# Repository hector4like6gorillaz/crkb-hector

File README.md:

# crkb-hector
diseños y pcb de teclados en eagle
Aqui tengo guardado lo que es mi pcb y esquematico de lo que viene a ser un teclado dividido en eagle cad soft tanto 
el lado derecho como el izquierdo diseñado en la version 8 del mismo programa antes mencionado

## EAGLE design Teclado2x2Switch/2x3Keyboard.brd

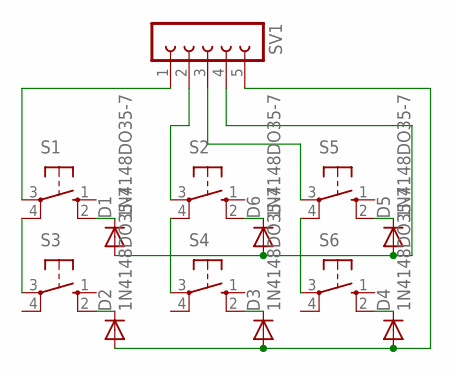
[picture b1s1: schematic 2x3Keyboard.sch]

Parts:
D1, D2, D3, D4, D5, D6: 1N4148DO35-7; DO35-7
S1, S2, S3, S4, S5, S6: 10-XX; B3F-10XX
SV1: FE05-1

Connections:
unnamed: S1.3, SV1.1
unnamed: S1.4 (P1), S3.3
unnamed: S2.4 (P1), S4.3
unnamed: S5.4 (P1), S6.3
unnamed: S2.3, SV1.2
unnamed: S5.3, SV1.3
unnamed: D1.C, S1.2 (S1)
unnamed: D6.C, S2.2 (S1)
unnamed: D5.C, S5.2 (S1)
unnamed: D4.C, S6.2 (S1)
unnamed: D3.C, S4.2 (S1)
unnamed: D2.C, S3.2 (S1)
unnamed: D2.A, D3.A, D4.A, SV1.5
unnamed: D1.A, D5.A, D6.A, SV1.4

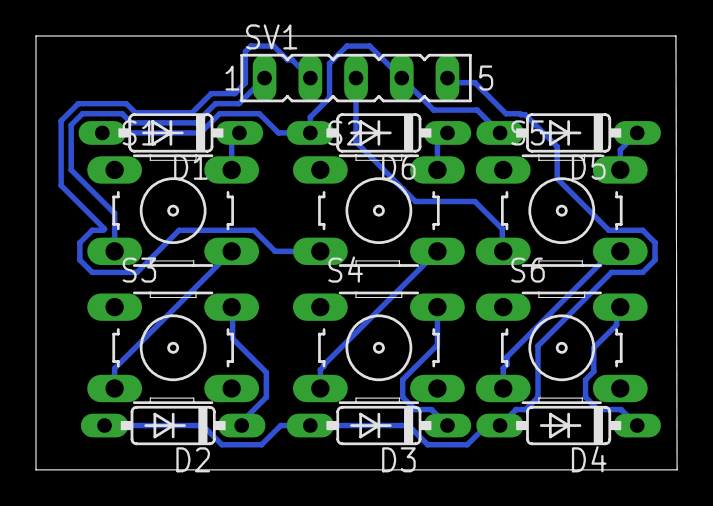
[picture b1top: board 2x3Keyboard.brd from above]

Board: 2 copper layers, 35.6 x 24.1 mm, 13 parts (0 on the bottom side), 14 nets.

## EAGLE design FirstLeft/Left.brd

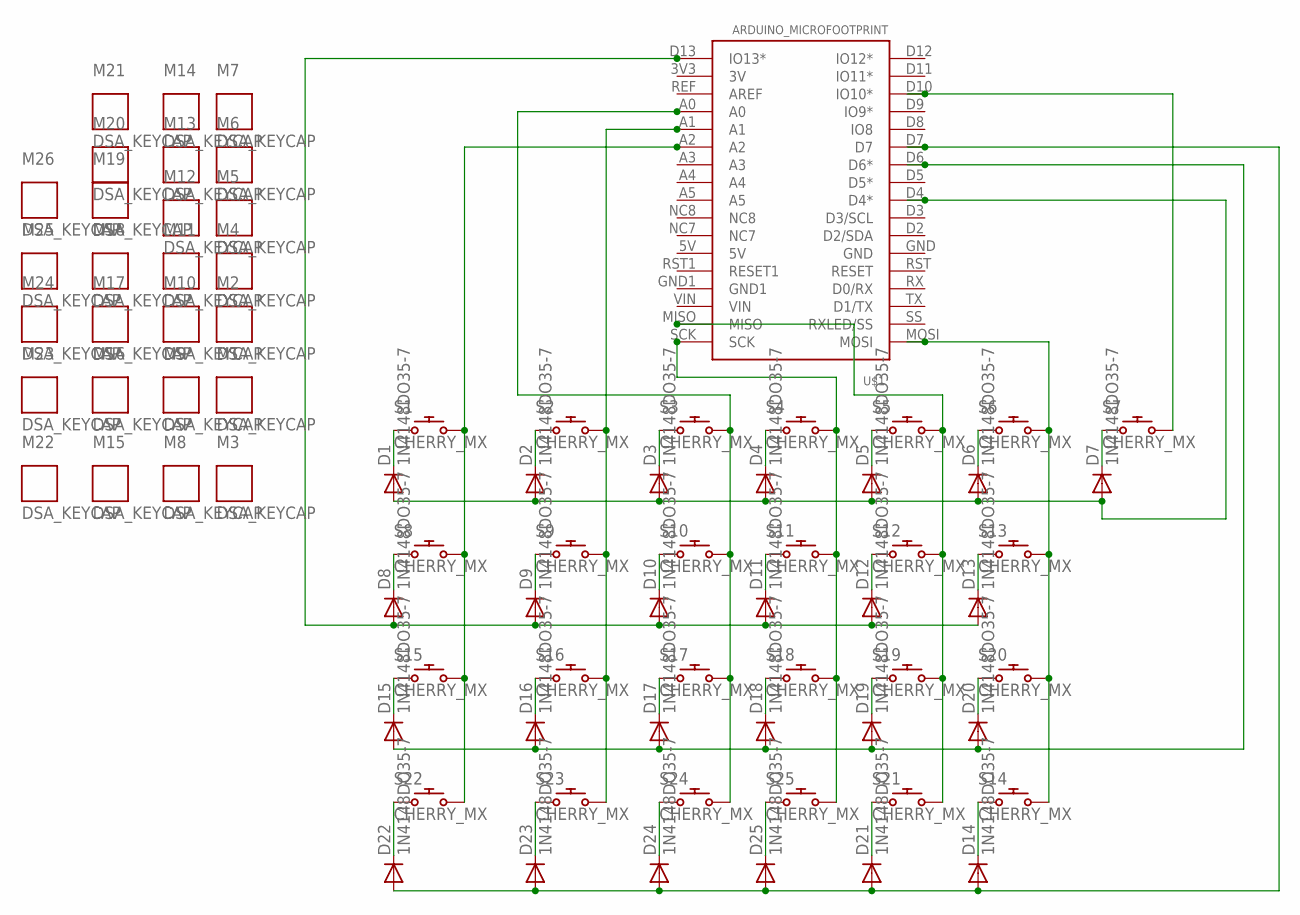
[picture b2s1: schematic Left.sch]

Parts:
D1, D2, D3, D4, D5, D6, D7, D8, D9, D10, D11, D12, D13, D14, D15, D16, D17, D18, D19, D20, D21, D22, D23, D24, D25: 1N4148DO35-7; DO35-7
M1, M2, M3, M4, M5, M6, M7, M8, M9, M10, M11, M12, M13, M14, M15, M16, M17, M18, M19, M20, M21, M22, M23, M24, M25, M26: DSA_KEYCAP
S1, S2, S3, S4, S5, S6, S7, S8, S9, S10, S11, S12, S13, S14, S15, S16, S17, S18, S19, S20, S21, S22, S23, S24, S25: CHERRY_MX
U$1: ARDUINO_MICROFOOTPRINT; ARDUINO-MICRO

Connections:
unnamed: D14.A, D21.A, D22.A, D23.A, D24.A, D25.A, U$1.D7
unnamed: D8.A, D9.A, D10.A, D11.A, D12.A, D13.A, U$1.D13 (IO13*)
unnamed: D12.C, S12.S1 (1)
unnamed: S1.S2 (2), S8.S2 (2), S15.S2 (2), S22.S2 (2), U$1.A2
unnamed: S2.S2 (2), S9.S2 (2), S16.S2 (2), S23.S2 (2), U$1.A1
unnamed: S3.S2 (2), S10.S2 (2), S17.S2 (2), S24.S2 (2), U$1.A0
unnamed: S4.S2 (2), S11.S2 (2), S18.S2 (2), S25.S2 (2), U$1.SCK
unnamed: S5.S2 (2), S12.S2 (2), S19.S2 (2), S21.S2 (2), U$1.MISO
unnamed: S6.S2 (2), S13.S2 (2), S14.S2 (2), S20.S2 (2), U$1.MOSI
unnamed: S7.S2 (2), U$1.D10 (IO10*)
unnamed: D1.C, S1.S1 (1)
unnamed: D8.C, S8.S1 (1)
unnamed: D15.C, S15.S1 (1)
unnamed: D22.C, S22.S1 (1)
unnamed: D23.C, S23.S1 (1)
unnamed: D16.C, S16.S1 (1)
unnamed: D9.C, S9.S1 (1)
unnamed: D2.C, S2.S1 (1)
unnamed: D3.C, S3.S1 (1)
unnamed: D10.C, S10.S1 (1)
unnamed: D17.C, S17.S1 (1)
unnamed: D24.C, S24.S1 (1)
unnamed: D25.C, S25.S1 (1)
unnamed: D18.C, S18.S1 (1)
unnamed: D11.C, S11.S1 (1)
unnamed: D4.C, S4.S1 (1)
unnamed: D5.C, S5.S1 (1)
unnamed: D6.C, S6.S1 (1)
unnamed: D7.C, S7.S1 (1)
unnamed: D14.C, S14.S1 (1)
unnamed: D13.C, S13.S1 (1)
unnamed: D19.C, S19.S1 (1)
unnamed: D20.C, S20.S1 (1)
unnamed: D21.C, S21.S1 (1)
unnamed: D15.A, D16.A, D17.A, D18.A, D19.A, D20.A, U$1.D6 (D6*)
unnamed: D1.A, D2.A, D3.A, D4.A, D5.A, D6.A, D7.A, U$1.D4 (D4*)

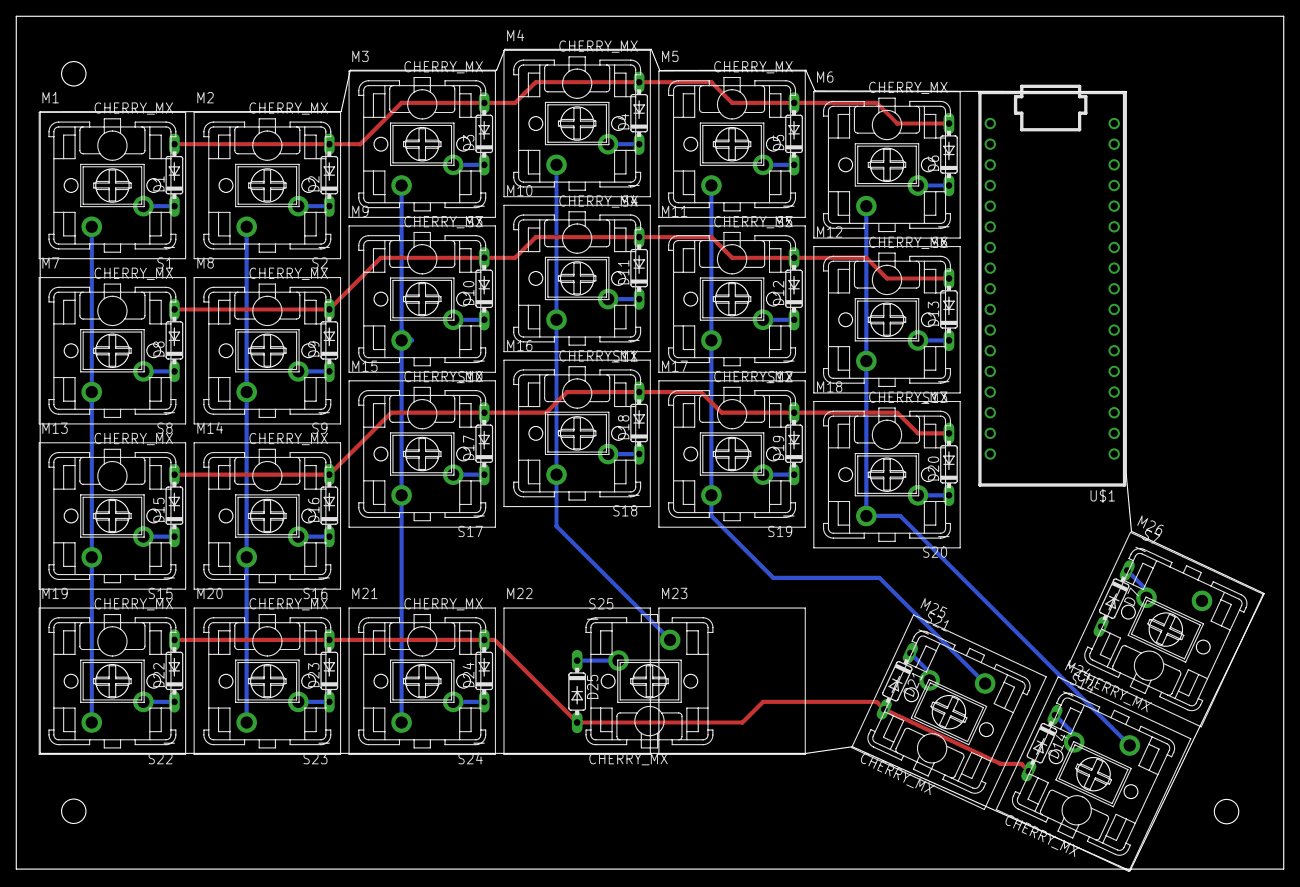
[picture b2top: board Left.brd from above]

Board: 2 copper layers, 155.9 x 105.1 mm, 77 parts (0 on the bottom side), 36 nets.

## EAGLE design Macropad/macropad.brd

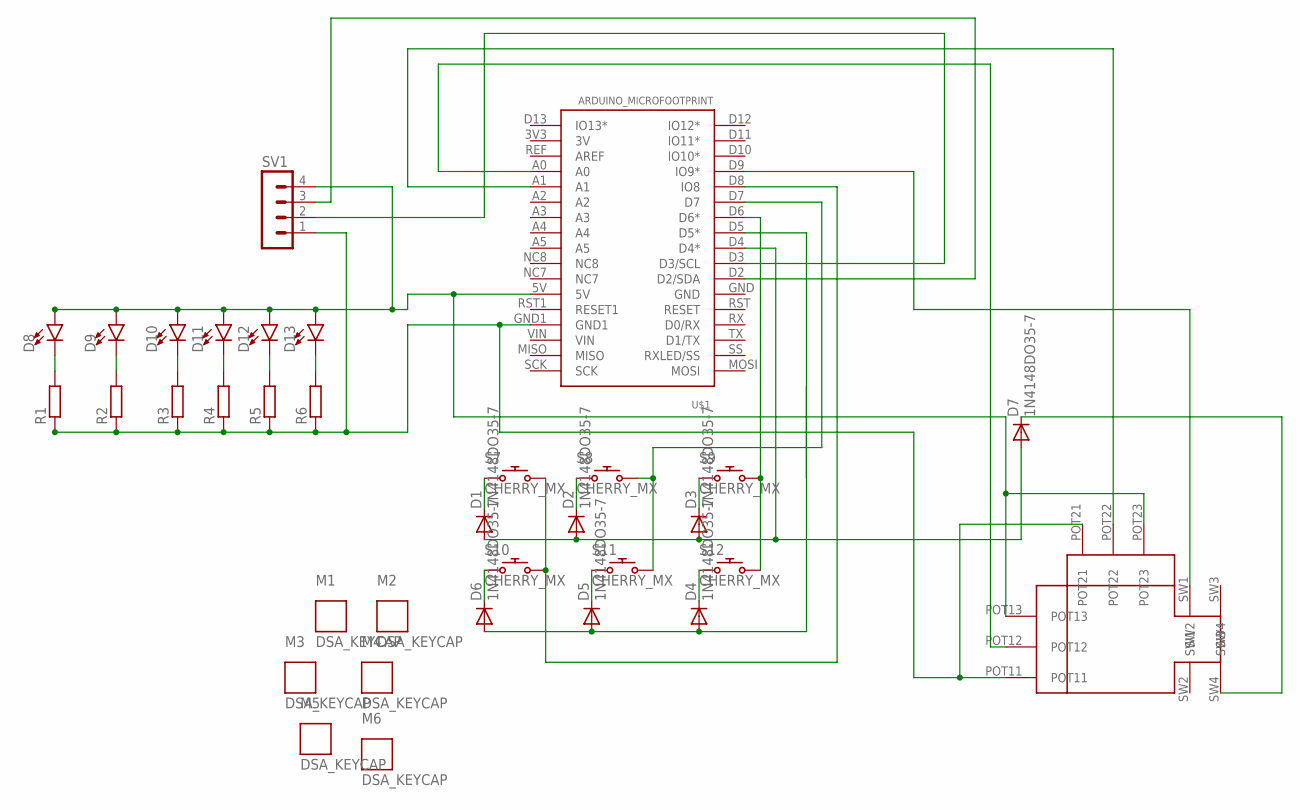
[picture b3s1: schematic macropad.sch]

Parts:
D1, D2, D3, D4, D5, D6, D7: 1N4148DO35-7; DO35-7
D8, D9, D10, D11, D12, D13: LED-3MM-NO_SILK; LED_3MM-NS
M1, M2, M3, M4, M5, M6: DSA_KEYCAP
R1, R2, R3, R4, R5, R6: R-EU_0204/7; 0204/7
S7, S8, S9, S10, S11, S12: CHERRY_MX
SV1: MA04-1
U$1: ARDUINO_MICROFOOTPRINT; ARDUINO-MICRO
U$2: JOYSTICK; JOYSTICKONE

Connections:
unnamed: D5.C, S11.S1 (1)
unnamed: D1.C, S7.S1 (1)
unnamed: D6.C, S10.S1 (1)
unnamed: S7.S2 (2), S10.S2 (2), U$1.D8 (IO8)
unnamed: D2.C, S8.S1 (1)
unnamed: D3.C, S9.S1 (1)
unnamed: SV1.2, U$1.D3 (D3/SCL)
unnamed: S9.S2 (2), S12.S2 (2), U$1.D6 (D6*)
unnamed: D7.C, U$2.SW4
unnamed: D1.A, D2.A, D3.A, D7.A, U$1.D4 (D4*)
unnamed: D4.A, D5.A, D6.A, U$1.D5 (D5*)
unnamed: SV1.3, U$1.D2 (D2/SDA)
unnamed: U$1.A0, U$2.POT12
unnamed: U$1.A1, U$2.POT22
unnamed: D4.C, S12.S1 (1)
unnamed: S8.S2 (2), S11.S2 (2), U$1.D7
unnamed: U$1.D9 (IO9*), U$2.SW1
unnamed: D8.A, D9.A, D10.A, D11.A, D12.A, D13.A, SV1.4, U$1.5V, U$2.POT13, U$2.POT23
unnamed: D8.K (C), R1.2
unnamed: D9.K (C), R2.2
unnamed: D10.K (C), R3.2
unnamed: D11.K (C), R4.2
unnamed: D12.K (C), R5.2
unnamed: D13.K (C), R6.2
unnamed: R1.1, R2.1, R3.1, R4.1, R5.1, R6.1, SV1.1, U$1.GND1, U$2.POT11, U$2.POT21

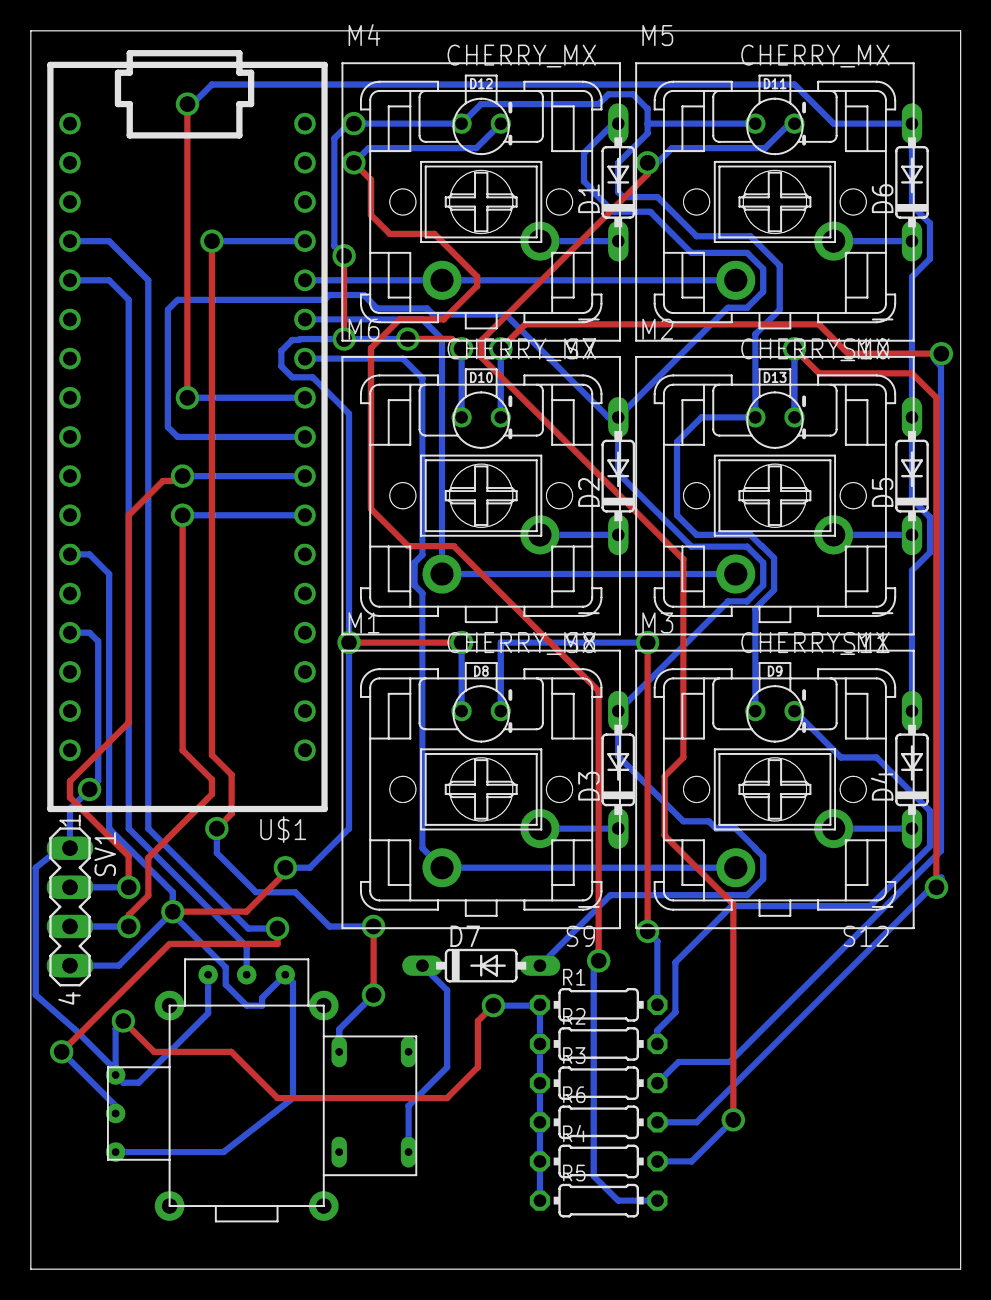
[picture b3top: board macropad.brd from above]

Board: 2 copper layers, 60.3 x 80.3 mm, 34 parts (0 on the bottom side), 25 nets.

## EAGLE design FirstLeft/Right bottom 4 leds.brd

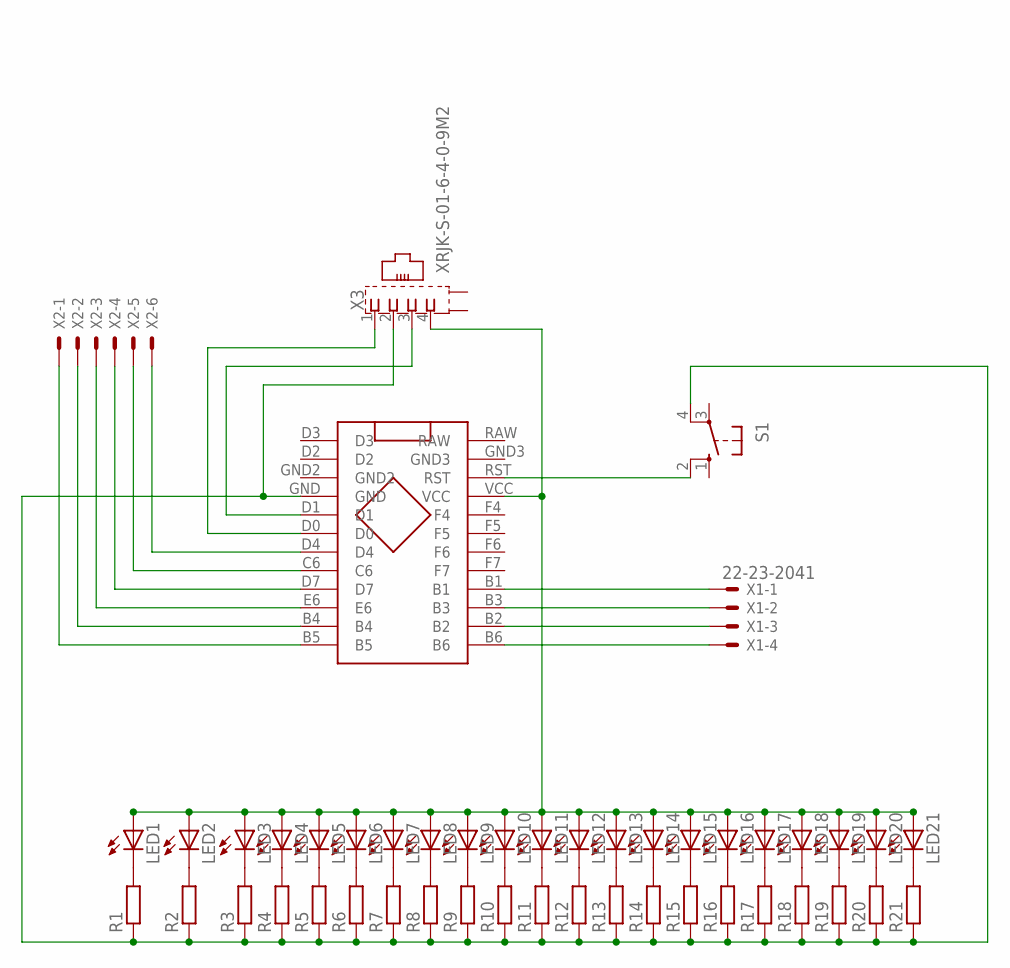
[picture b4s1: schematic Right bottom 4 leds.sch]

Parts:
LED1, LED2, LED3, LED4, LED5, LED6, LED7, LED8, LED9, LED10, LED11, LED12, LED13, LED14, LED15, LED16, LED17, LED18, LED19, LED20, LED21: LED3MM
R1, R2, R3, R4, R5, R6, R7, R8, R9, R10, R11, R12, R13, R14, R15, R16, R17, R18, R19, R20, R21: R-EU_0204/7; 0204/7
S1: 10-XX; B3F-10XX
U$1: ARDUINO_PRO_MICRO_HECTOR
X1: 22-23-2041
X2: 22-23-2061
X3: XRJK-S-01-6-4-0-9M2

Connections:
unnamed: LED3.K (C), R3.2
unnamed: LED4.K (C), R4.2
unnamed: LED5.K (C), R5.2
unnamed: LED2.K (C), R2.2
unnamed: LED1.K (C), R1.2
unnamed: LED6.K (C), R6.2
unnamed: LED7.K (C), R7.2
unnamed: LED8.K (C), R8.2
unnamed: LED9.K (C), R9.2
unnamed: LED10.K (C), R10.2
unnamed: LED11.K (C), R11.2
unnamed: LED12.K (C), R12.2
unnamed: LED13.K (C), R13.2
unnamed: LED14.K (C), R14.2
unnamed: LED15.K (C), R15.2
unnamed: LED16.K (C), R16.2
unnamed: LED17.K (C), R17.2
unnamed: LED18.K (C), R18.2
unnamed: LED19.K (C), R19.2
unnamed: LED20.K (C), R20.2
unnamed: LED21.K (C), R21.2
unnamed: S1.2 (S1), U$1.RST
unnamed: U$1.B5, X2.1
unnamed: U$1.B4, X2.2
unnamed: U$1.E6, X2.3
unnamed: U$1.D7, X2.4
unnamed: U$1.C6, X2.5
unnamed: U$1.D4, X2.6
unnamed: U$1.D0, X3.1
unnamed: U$1.D1, X3.3
unnamed: R1.1, R2.1, R3.1, R4.1, R5.1, R6.1, R7.1, R8.1, R9.1, R10.1, R11.1, R12.1, R13.1, R14.1, R15.1, R16.1, R17.1, R18.1, R19.1, R20.1, R21.1, S1.4 (P1), U$1.GND, X3.2
unnamed: LED1.A, LED2.A, LED3.A, LED4.A, LED5.A, LED6.A, LED7.A, LED8.A, LED9.A, LED10.A, LED11.A, LED12.A, LED13.A, LED14.A, LED15.A, LED16.A, LED17.A, LED18.A, LED19.A, LED20.A, LED21.A, U$1.VCC, X3.4
unnamed: U$1.B6, X1.4
unnamed: U$1.B2, X1.3
unnamed: U$1.B3, X1.2
unnamed: U$1.B1, X1.1

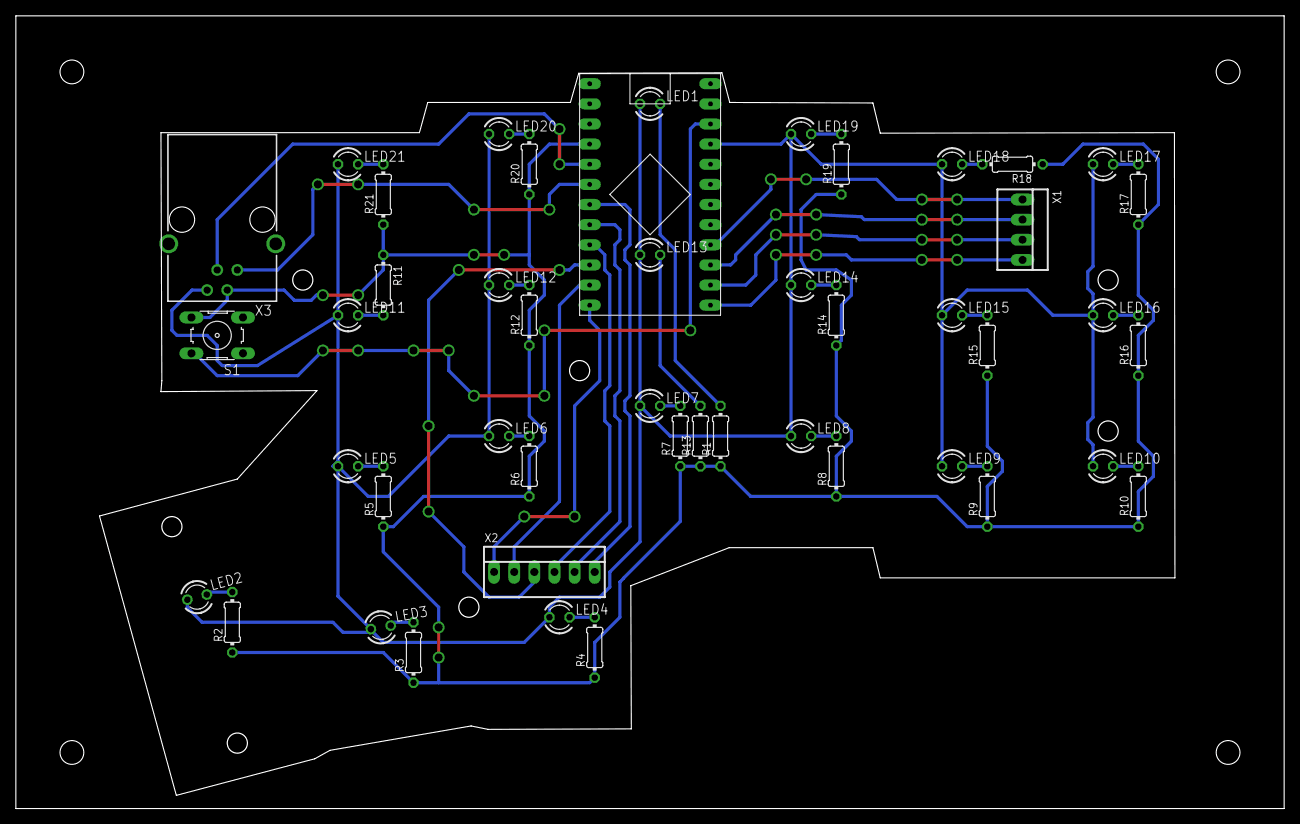
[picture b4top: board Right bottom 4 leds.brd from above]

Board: 2 copper layers, 159.8 x 99.8 mm, 47 parts (0 on the bottom side), 36 nets.

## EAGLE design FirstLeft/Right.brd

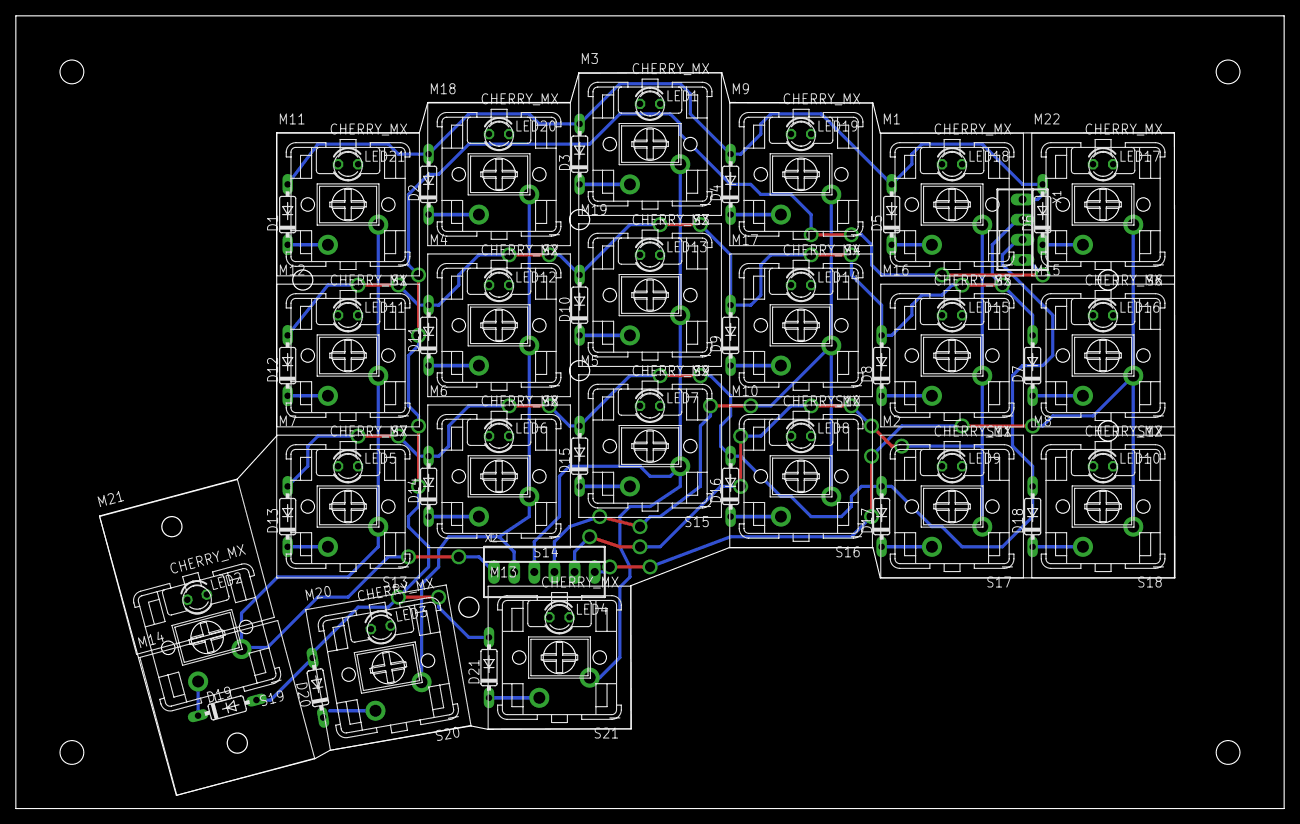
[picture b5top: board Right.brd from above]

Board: 2 copper layers, 159.8 x 99.8 mm, 87 parts (0 on the bottom side), 31 nets.

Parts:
D1, D2, D3, D4, D5, D6, D7, D8, D9, D10, D11, D12, D13, D14, D15, D16, D17, D18, D19, D20, D21: 1N4148DO35-7; DO35-7
LED1, LED2, LED3, LED4, LED5, LED6, LED7, LED8, LED9, LED10, LED11, LED12, LED13, LED14, LED15, LED16, LED17, LED18, LED19, LED20, LED21: LED3MM
M1, M2, M3, M4, M5, M6, M7, M8, M9, M10, M11, M12, M13, M14, M15, M16, M17, M18, M19, M20, M21, M22: DSA_KEYCAP
S1, S2, S3, S4, S5, S6, S7, S8, S9, S10, S11, S12, S13, S14, S15, S16, S17, S18, S19, S20, S21: CHERRY_MX
X1: 22-23-2041
X2: 22-23-2061

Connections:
unnamed: D1.C, S1.S2
unnamed: D2.C, S2.S2
unnamed: D3.C, S3.S2
unnamed: D4.C, S4.S2
unnamed: D5.C, S5.S2
unnamed: D6.C, S6.S2
unnamed: D7.C, S12.S2
unnamed: D8.C, S11.S2
unnamed: D9.C, S10.S2
unnamed: D10.C, S9.S2
unnamed: D11.C, S8.S2
unnamed: D12.C, S7.S2
unnamed: D13.C, S13.S2
unnamed: D14.C, S14.S2
unnamed: D15.C, S15.S2
unnamed: D16.C, S16.S2
unnamed: D17.C, S17.S2
unnamed: D18.C, S18.S2
unnamed: D19.C, S19.S2
unnamed: D20.C, S20.S2
unnamed: D21.C, S21.S2
unnamed: S3.S1, S9.S1, S15.S1, S21.S1, X2.3
unnamed: S2.S1, S8.S1, S14.S1, S20.S1, X2.2
unnamed: S1.S1, S7.S1, S13.S1, S19.S1, X2.1
unnamed: S4.S1, S10.S1, S16.S1, X2.4
unnamed: S5.S1, S11.S1, S17.S1, X2.5
unnamed: S6.S1, S12.S1, S18.S1, X2.6
unnamed: D19.A, D20.A, D21.A, X1.4
unnamed: D13.A, D14.A, D15.A, D16.A, D17.A, D18.A, X1.3
unnamed: D7.A, D8.A, D9.A, D10.A, D11.A, D12.A, X1.2
unnamed: D1.A, D2.A, D3.A, D4.A, D5.A, D6.A, X1.1

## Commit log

2021-06-11 keyboard tipo corne y demas teclados
2021-10-01 Add files via upload
    add logo

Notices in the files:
parts and their libraries:
ws2812b: Licensing: Creative Commons ShareAlike 4.0 International - https://creativecommons.org/licenses/by-sa/4.0
